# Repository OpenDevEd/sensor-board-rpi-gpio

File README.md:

# sensor-board-rpi-gpio

This is a breakout board for the Raspberry Pi GPIO. The purpose of the board is to testing several sensor sensor breakouts available in the UK, including the following:
* AHT20 (Adafruit)
* BH1750 (DFRobot/Femion)
* ENS160 (DFRobot/Femion)
* I2S MEMS Mic (Adafruit)
* I2S MEMS Mic (DFRobot/Femion)
* LTR-559 (Pimoroni)
* MCP9808 (Adafruit)
* SHT31 (Adafruit)
* SHT40/45 (Adafruit)
* SCD40/41 (Adafruit, Pimoroni, ebay)

Certain GPIO are not utilised by the board, because the board is meant to function with the Adafruit LoRa Bonnet (and PiJuice Zero).

Motivation: https://opendeved.net/ilce

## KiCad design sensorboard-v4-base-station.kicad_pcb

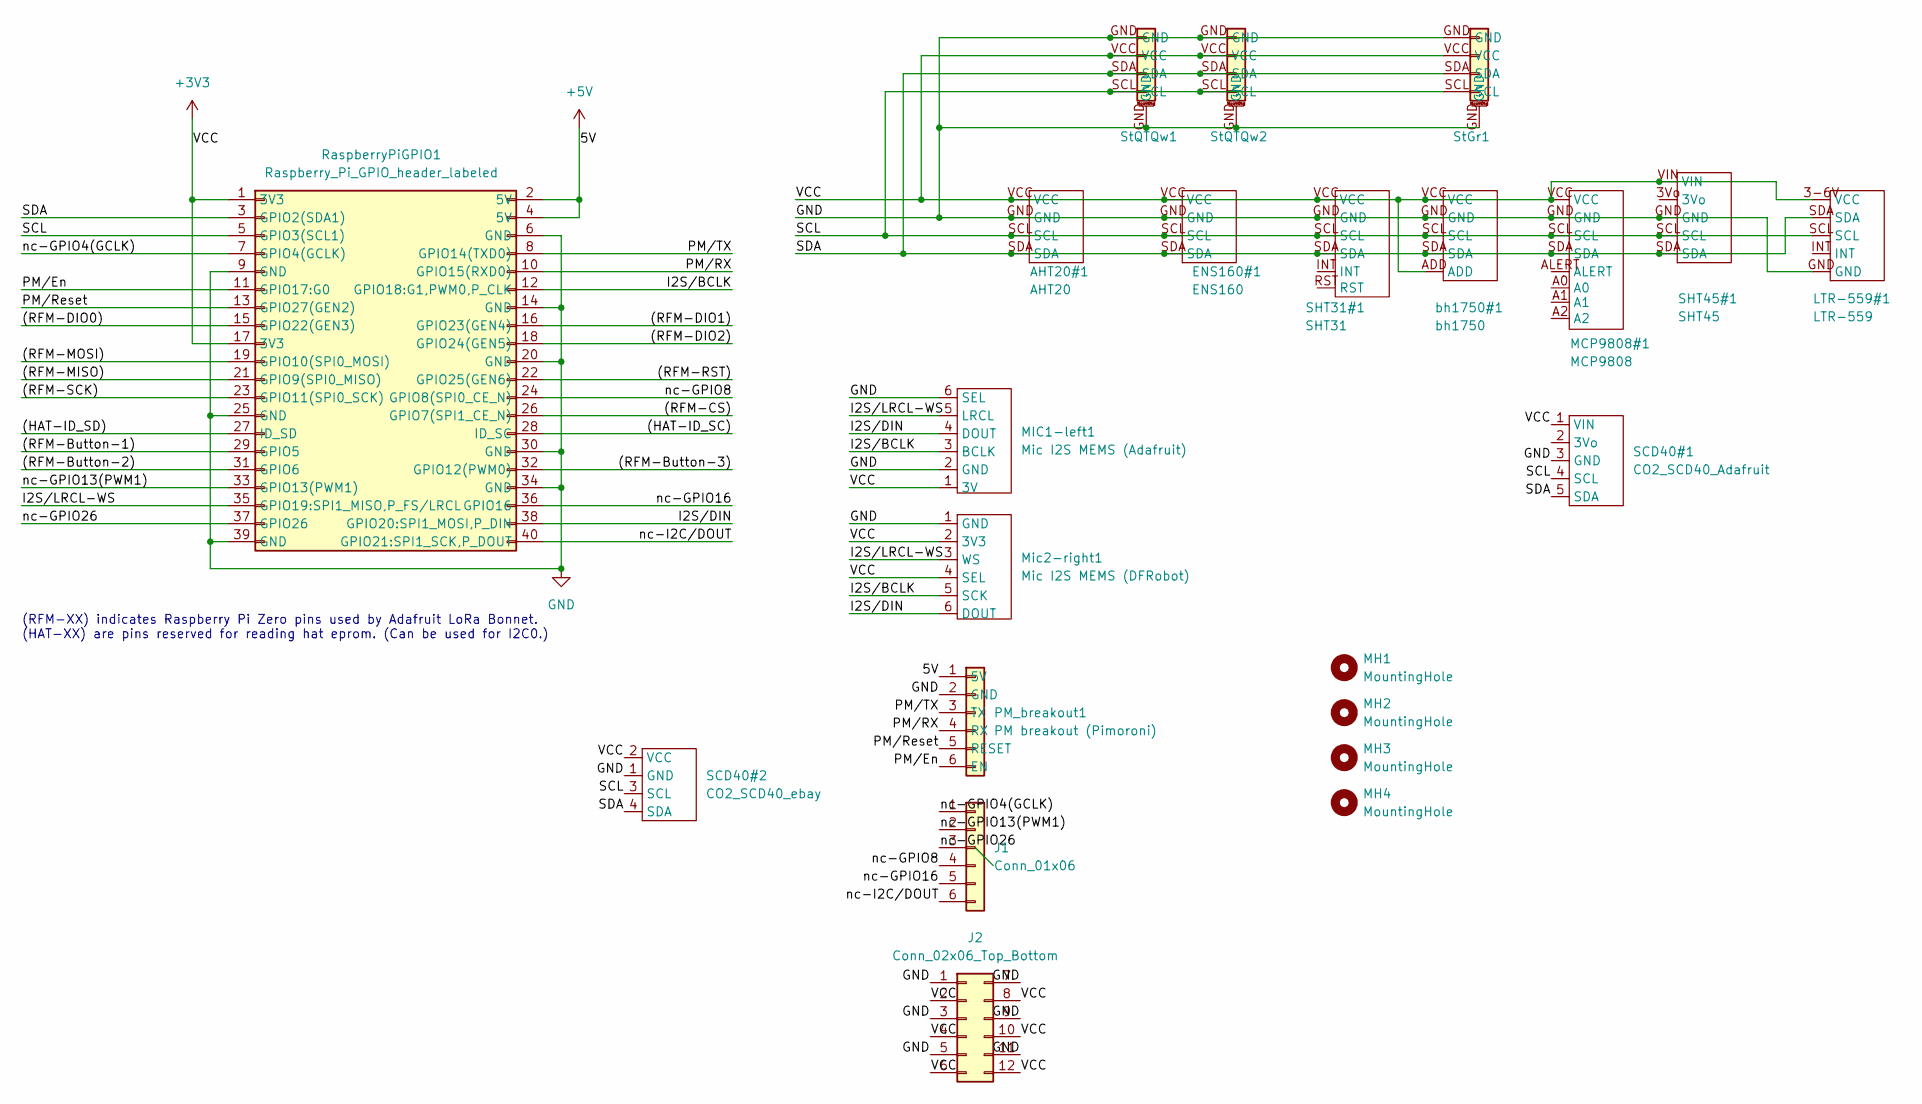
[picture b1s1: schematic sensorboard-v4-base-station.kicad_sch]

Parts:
AHT20#1: AHT20; AHT20 (Adafruit)
ENS160#1: ENS160; ENS160 (DFROBOT, Fermion), i2c pads
J1: Conn_01x06; PinHeader_1x06_P2.54mm_Vertical
J2: Conn_02x06_Top_Bottom; PinHeader_2x06_P2.54mm_Vertical; LCSC C6332209
LTR-559#1: LTR-559; LTR-559 (Pimoroni)
MCP9808#1: MCP9808; MCP9808 (Adafruit, original version)
MH1, MH2, MH3, MH4: MountingHole
MIC1-left1: Mic I2S MEMS (Adafruit)
Mic2-right1: Mic I2S MEMS (DFRobot)
PM_breakout1: PM breakout (Pimoroni); Particulate Matter Sensor Breakout (for PMS5003)
RaspberryPiGPIO1: Raspberry_Pi_GPIO_header_labeled; PinHeader_2x20_P2.54mm_Vertical; LCSC C5224014
SCD40#1: CO2_SCD40_Adafruit; SCD40 CO2 (Adafruit)
SCD40#2: CO2_SCD40_ebay; SCD40 CO2 (ebay)
SHT31#1: SHT31; SHT31 (DFR, Fermion)
SHT45#1: SHT45; SHT45 (Adafruit)
StGr1: Stemma-Grove (full size, horizontal); LCSC C519170
StQTQw1, StQTQw2: StemmaQT-Qwiic (horizontal); LCSC C145956
bh1750#1: bh1750; bh1750 (DFROBOT, Fermion)

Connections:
+3V3: AHT20#1.VCC, ENS160#1.VCC, J2.2, J2.4, J2.6, J2.8, J2.10, J2.12, LTR-559#1.3-6V (VCC), MCP9808#1.VCC, MIC1-left1.1 (3V), Mic2-right1.2 (3V3), Mic2-right1.4 (SEL), RaspberryPiGPIO1.1 (3V3), RaspberryPiGPIO1.17 (3V3), SCD40#1.1 (VIN), SCD40#2.2 (VCC), SHT31#1.VCC, SHT45#1.VIN, StGr1.VCC, StQTQw1.VCC, StQTQw2.VCC, bh1750#1.ADD, bh1750#1.VCC
+5V: PM_breakout1.1 (5V), RaspberryPiGPIO1.2 (5V), RaspberryPiGPIO1.4 (5V)
/(HAT-ID_SC): RaspberryPiGPIO1.28 (ID_SC)
/(HAT-ID_SD): RaspberryPiGPIO1.27 (ID_SD)
/(RFM-Button-1): RaspberryPiGPIO1.29 (GPIO5)
/(RFM-Button-2): RaspberryPiGPIO1.31 (GPIO6)
/(RFM-Button-3): RaspberryPiGPIO1.32 (GPIO12(PWM0))
/(RFM-CS): RaspberryPiGPIO1.26 (GPIO7(SPI1_CE_N))
/(RFM-DIO0): RaspberryPiGPIO1.15 (GPIO22(GEN3))
/(RFM-DIO1): RaspberryPiGPIO1.16 (GPIO23(GEN4))
/(RFM-DIO2): RaspberryPiGPIO1.18 (GPIO24(GEN5))
/(RFM-MISO): RaspberryPiGPIO1.21 (GPIO9(SPI0_MISO))
/(RFM-MOSI): RaspberryPiGPIO1.19 (GPIO10(SPI0_MOSI))
/(RFM-RST): RaspberryPiGPIO1.22 (GPIO25(GEN6))
/(RFM-SCK): RaspberryPiGPIO1.23 (GPIO11(SPI0_SCK))
/I2S/BCLK: MIC1-left1.3 (BCLK), Mic2-right1.5 (SCK), RaspberryPiGPIO1.12 (GPIO18:G1,PWM0,P_CLK)
/I2S/DIN: MIC1-left1.4 (DOUT), Mic2-right1.6 (DOUT), RaspberryPiGPIO1.38 (GPIO20:SPI1_MOSI,P_DIN)
/I2S/LRCL-WS: MIC1-left1.5 (LRCL), Mic2-right1.3 (WS), RaspberryPiGPIO1.35 (GPIO19:SPI1_MISO,P_FS/LRCL)
/PM/En: PM_breakout1.6 (EN), RaspberryPiGPIO1.11 (GPIO17:G0)
/PM/RX: PM_breakout1.4 (RX), RaspberryPiGPIO1.10 (GPIO15(RXD0))
/PM/Reset: PM_breakout1.5 (RESET), RaspberryPiGPIO1.13 (GPIO27(GEN2))
/PM/TX: PM_breakout1.3 (TX), RaspberryPiGPIO1.8 (GPIO14(TXD0))
/SCL: AHT20#1.SCL, ENS160#1.SCL, LTR-559#1.SCL, MCP9808#1.SCL, RaspberryPiGPIO1.5 (GPIO3(SCL1)), SCD40#1.4 (SCL), SCD40#2.3 (SCL), SHT31#1.SCL, SHT45#1.SCL, StGr1.SCL, StQTQw1.SCL, StQTQw2.SCL, bh1750#1.SCL
/SDA: AHT20#1.SDA, ENS160#1.SDA, LTR-559#1.SDA, MCP9808#1.SDA, RaspberryPiGPIO1.3 (GPIO2(SDA1)), SCD40#1.5 (SDA), SCD40#2.4 (SDA), SHT31#1.SDA, SHT45#1.SDA, StGr1.SDA, StQTQw1.SDA, StQTQw2.SDA, bh1750#1.SDA
/nc-GPIO4(GCLK): J1.1, RaspberryPiGPIO1.7 (GPIO4(GCLK))
/nc-GPIO8: J1.4, RaspberryPiGPIO1.24 (GPIO8(SPI0_CE_N))
/nc-GPIO13(PWM1): J1.2, RaspberryPiGPIO1.33 (GPIO13(PWM1))
/nc-GPIO16: J1.5, RaspberryPiGPIO1.36 (GPIO16)
/nc-GPIO26: J1.3, RaspberryPiGPIO1.37 (GPIO26)
/nc-I2C/DOUT: J1.6, RaspberryPiGPIO1.40 (GPIO21:SPI1_SCK,P_DOUT)
GND: AHT20#1.GND, ENS160#1.GND, J2.1, J2.3, J2.5, J2.7, J2.9, J2.11, LTR-559#1.GND, MCP9808#1.GND, MIC1-left1.2 (GND), MIC1-left1.6 (SEL), Mic2-right1.1 (GND), PM_breakout1.2 (GND), RaspberryPiGPIO1.6 (GND), RaspberryPiGPIO1.9 (GND), RaspberryPiGPIO1.14 (GND), RaspberryPiGPIO1.20 (GND), RaspberryPiGPIO1.25 (GND), RaspberryPiGPIO1.30 (GND), RaspberryPiGPIO1.34 (GND), RaspberryPiGPIO1.39 (GND), SCD40#1.3 (GND), SCD40#2.1 (GND), SHT31#1.GND, SHT45#1.GND, StGr1.GND, StQTQw1.GND, StQTQw2.GND, bh1750#1.GND

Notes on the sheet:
(RFM-XX) indicates Raspberry Pi Zero pins used by Adafruit LoRa Bonnet. (HAT-XX) are pins reserved for reading hat eprom. (Can be used for I2C0.)

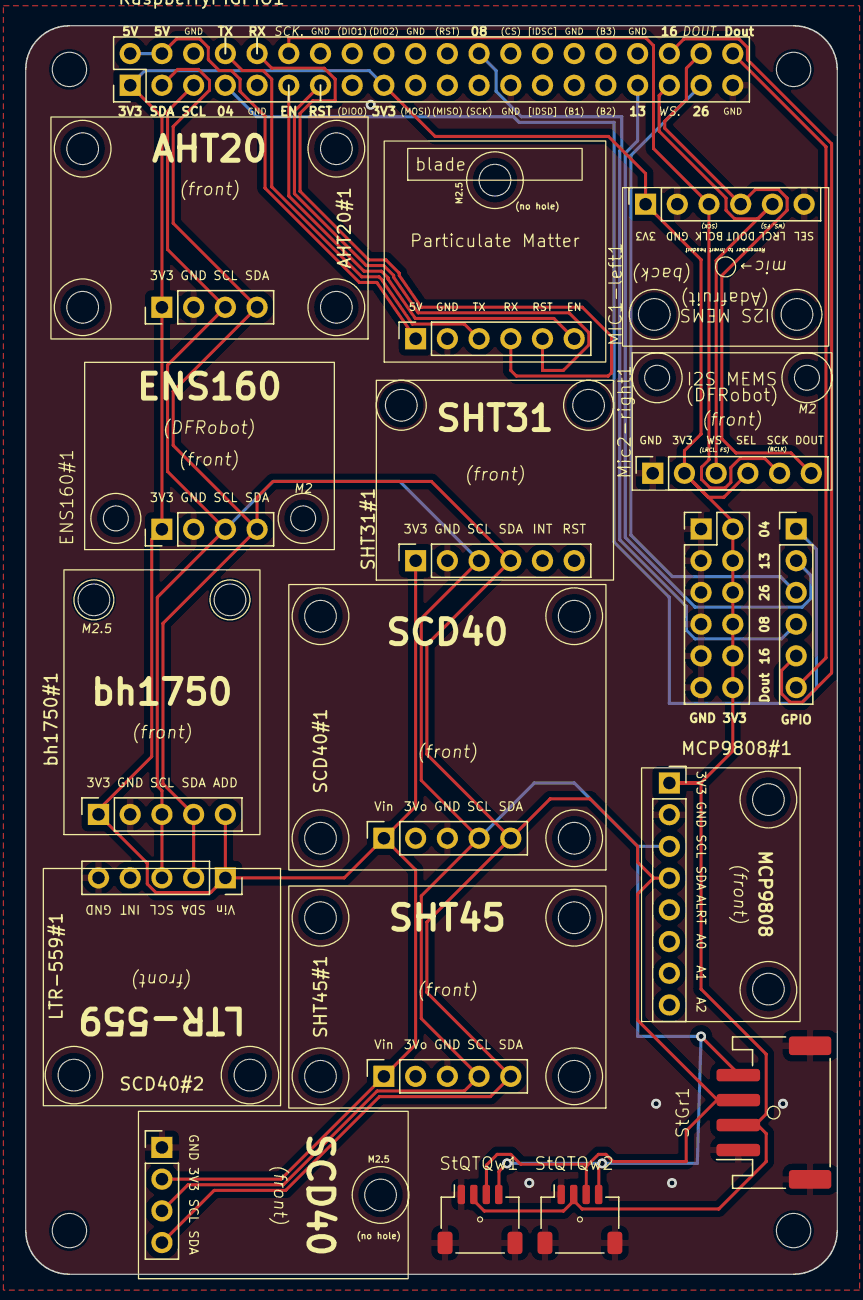
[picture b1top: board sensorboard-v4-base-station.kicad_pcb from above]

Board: 2 copper layers, 65.0 x 100.0 mm, 22 parts (0 on the bottom side), 18 nets.
